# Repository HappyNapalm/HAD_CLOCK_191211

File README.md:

# HAD_CLOCK_191211 #
Clock for HAD Contest

## TODO ##
* Final verification of footprints. Last time!
* Sort out transformer
* Design an enclosure
* Add buttons to program the time (Research cap touch)
* Convert Mouser Project into csv

~~Microcontroller Corrections to PIC18F45K20~~

~~Consider making a version for the LPC804 as well as the PIC~~

~~Consider making multiple sheets for the schematic~~

~~Redo the outline in 4 x 15 pattern instead of a 3 x 20 pattern~~

## Parts to Select ##
* Transformer
* Diodes
* Resist0r 0603 100 ohm for 20 mAs at 3v3. 72 resistors

~~Shift Register (Affects resistor size)~~

~~Full rectifier~~

## Brief License ##
* Non-comericial
* Unlimited remakes for personal use
* Cite this project as source for any re-mixes

### Online Resources ###
https://www.pcbway.com/pcb_prototype/What_are_Plated_Half_Holes_Castellated_Holes_.html

### KiCAD Renders ###

Front | Back
:-------:|:------:
![Clock Front] (https://github.com/HappyNapalm/HAD_CLOCK_191211/blob/pic18/front.png)  |  ![Clock Rear] (https://github.com/HappyNapalm/HAD_CLOCK_191211/blob/pic18/rear.png)

![LED Test Front] (../renders/01_LED_test/front.png)

![LED Test Rear] (../renders/01_LED_test/rear.png)

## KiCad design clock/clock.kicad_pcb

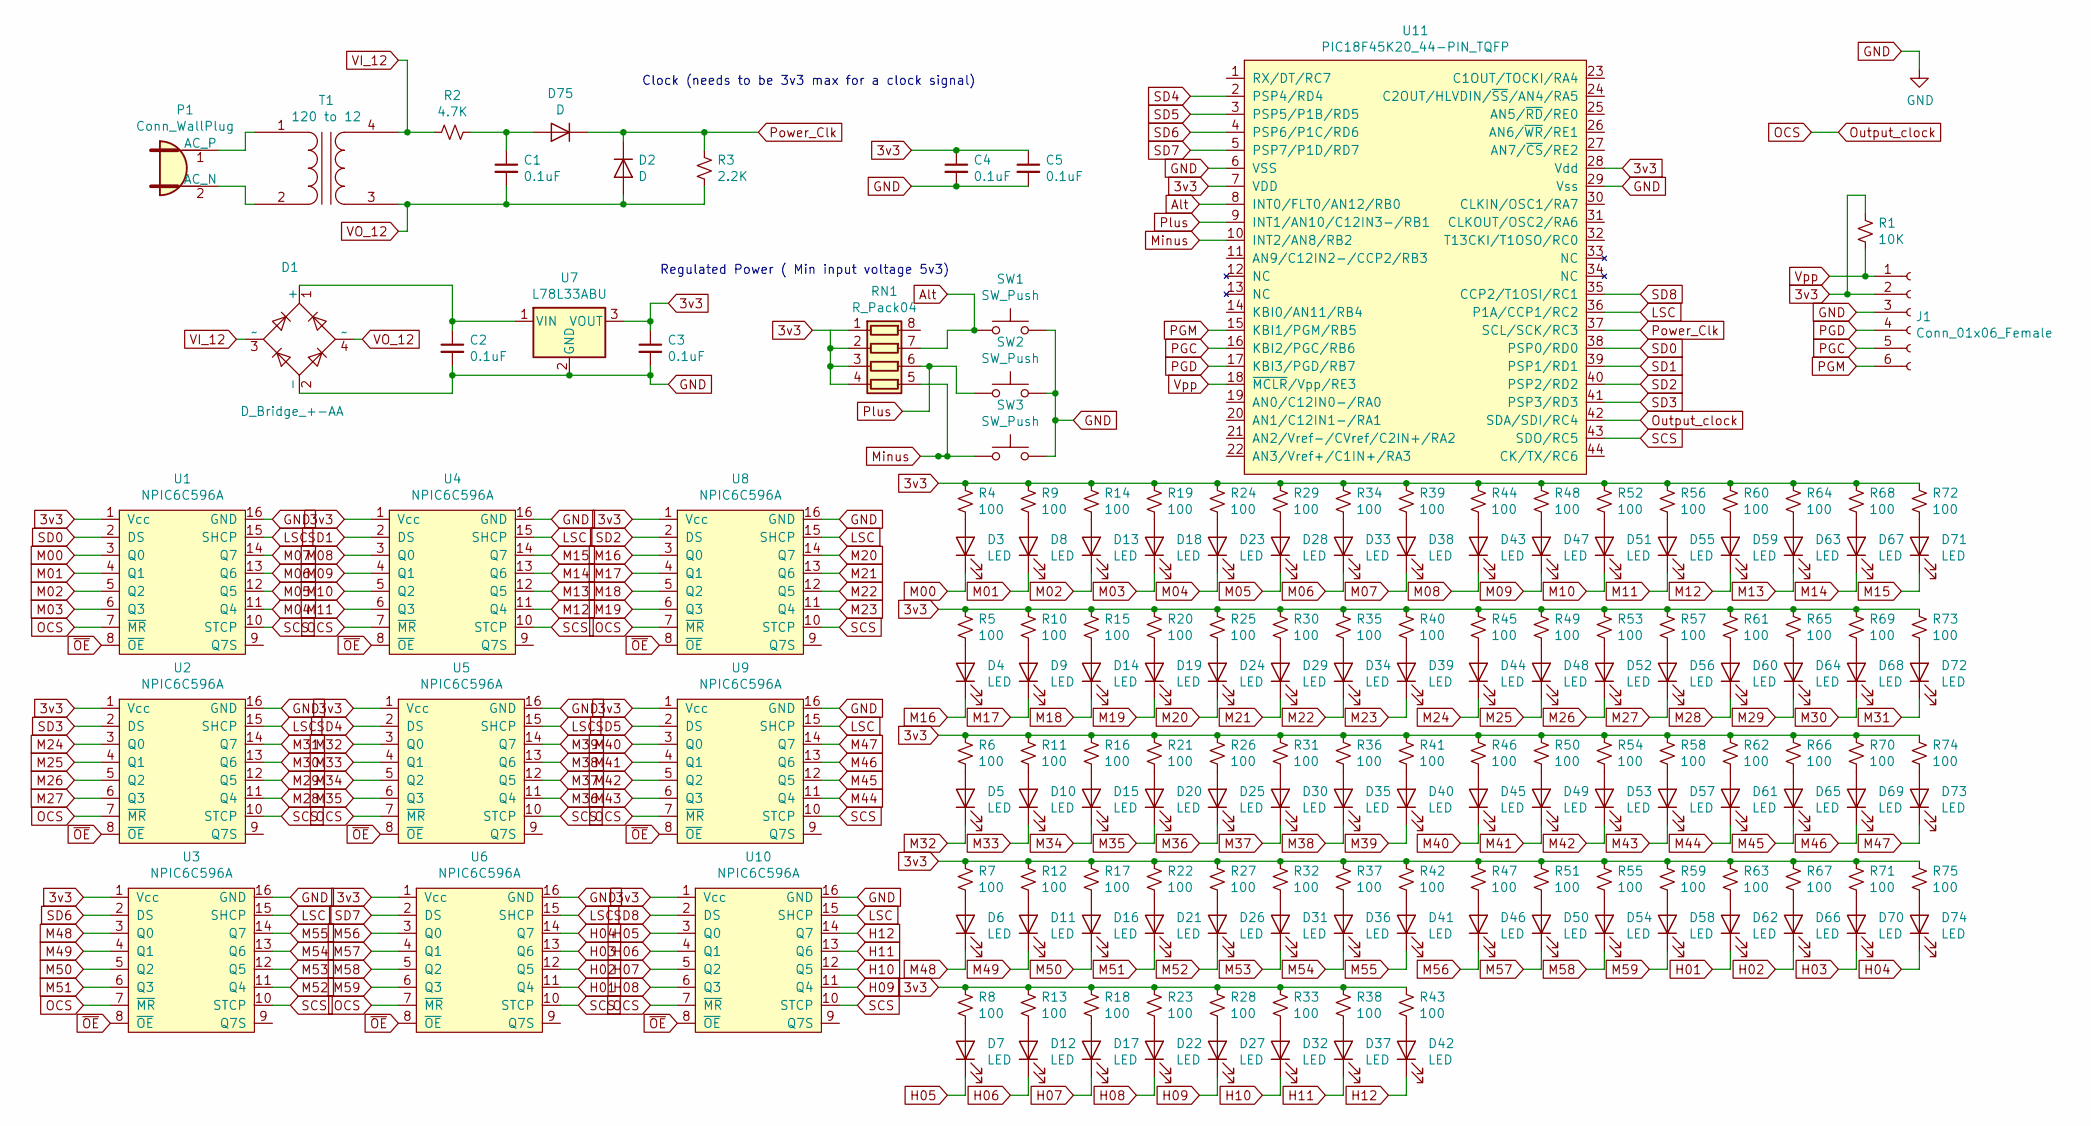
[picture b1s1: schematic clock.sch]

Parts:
C1, C2, C3, C4, C5: 0.1uF; C_0805_2012Metric
D1: D_Bridge_+-AA; Diode_Bridge_Diotec_ABS
D2, D75: D; D_0805_2012Metric
D3, D4, D5, D6, D7, D8, D9, D10, D11, D12, D13, D14, D15, D16, D17, D18, D19, D20, D21, D22, D23, D24, D25, D26, D27, D28, D29, D30, D31, D32, D33, D34, D35, D36, D37, D38, D39, D40, D41, D42, D43, D44, D45, D46, D47, D48, D49, D50, D51, D52, D53, D54, D55, D56, D57, D58, D59, D60, D61, D62, D63, D64, D65, D66, D67, D68, D69, D70, D71, D72, D73, D74: LED; LTST-S110KGKT_castellated_silkV1_rounded_rec
J1: Conn_01x06_Female; PinHeader_1x06_P2.54mm_Vertical
P1: Conn_WallPlug; PhoenixContact_GMSTBA_2,5_2-G-7,62_1x02_P7.62mm_Horizontal
R1: 10K; R_0805_2012Metric
R2: 4.7K; R_Axial_DIN0204_L3.6mm_D1.6mm_P7.62mm_Horizontal
R3: 2.2K; R_Axial_DIN0204_L3.6mm_D1.6mm_P7.62mm_Horizontal
R4, R5, R6, R7, R8, R9, R10, R11, R12, R13, R14, R15, R16, R17, R18, R19, R20, R21, R22, R23, R24, R25, R26, R27, R28, R29, R30, R31, R32, R33, R34, R35, R36, R37, R38, R39, R40, R41, R42, R43, R44, R45, R46, R47, R48, R49, R50, R51, R52, R53, R54, R55, R56, R57, R58, R59, R60, R61, R62, R63, R64, R65, R66, R67, R68, R69, R70, R71, R72, R73, R74, R75: 100; R_0603_1608Metric
RN1: R_Pack04; R_Array_Concave_4x0603
SW1, SW2, SW3: SW_Push; LL3301FF065QJ
T1: 120 to 12; TerminalBlock_bornier-2_P5.08mm
U1, U2, U3, U4, U5, U6, U8, U9, U10: NPIC6C596A; TSSOP-16_4.4x5mm_P0.65mm
U7: L78L33ABU; SOT-89-3
U11: PIC18F45K20_44-PIN_TQFP; TQFP-44_10x10mm_P0.8mm

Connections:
3v3: C3.1, C4.1, C5.1, J1.2, R1.1, R4.1, R5.1, R6.1, R7.1, R8.1, R9.1, R10.1, R11.1, R12.1, R13.1, R14.1, R15.1, R16.1, R17.1, R18.1, R19.1, R20.1, R21.1, R22.1, R23.1, R24.1, R25.1, R26.1, R27.1, R28.1, R29.1, R30.1, R31.1, R32.1, R33.1, R34.1, R35.1, R36.1, R37.1, R38.1, R39.1, R40.1, R41.1, R42.1, R43.1, R44.1, R45.1, R46.1, R47.1, R48.1, R49.1, R50.1, R51.1, R52.1, R53.1, R54.1, R55.1, R56.1, R57.1, R58.1, R59.1, R60.1, R61.1, R62.1, R63.1, R64.1, R65.1, R66.1, R67.1, R68.1, R69.1, R70.1, R71.1, R72.1, R73.1, R74.1, R75.1, RN1.1 (R1.1), RN1.2 (R2.1), RN1.3 (R3.1), RN1.4 (R4.1), U1.1 (Vcc), U2.1 (Vcc), U3.1 (Vcc), U4.1 (Vcc), U5.1 (Vcc), U6.1 (Vcc), U7.3 (VOUT), U8.1 (Vcc), U9.1 (Vcc), U10.1 (Vcc), U11.7 (VDD), U11.28 (Vdd)
Alt: RN1.7 (R2.2), SW1.1, U11.8 (INT0/FLT0/AN12/RB0)
GND: C2.2, C3.2, C4.2, C5.2, D1.2 (-), J1.3, SW1.2, SW2.2, SW3.2, U1.16 (GND), U2.16 (GND), U3.16 (GND), U4.16 (GND), U5.16 (GND), U6.16 (GND), U7.2 (GND), U8.16 (GND), U9.16 (GND), U10.16 (GND), U11.6 (VSS), U11.29 (Vss)
H01: D62.1 (K), U6.11 (Q4)
H02: D66.1 (K), U6.12 (Q5)
H03: D70.1 (K), U6.13 (Q6)
H04: D74.1 (K), U6.14 (Q7)
H05: D7.1 (K), U10.3 (Q0)
H06: D12.1 (K), U10.4 (Q1)
H07: D17.1 (K), U10.5 (Q2)
H08: D22.1 (K), U10.6 (Q3)
H09: D27.1 (K), U10.11 (Q4)
H10: D32.1 (K), U10.12 (Q5)
H11: D37.1 (K), U10.13 (Q6)
H12: D42.1 (K), U10.14 (Q7)
LSC: U1.15 (SHCP), U2.15 (SHCP), U3.15 (SHCP), U4.15 (SHCP), U5.15 (SHCP), U6.15 (SHCP), U8.15 (SHCP), U9.15 (SHCP), U10.15 (SHCP), U11.36 (P1A/CCP1/RC2)
M00: D3.1 (K), U1.3 (Q0)
M01: D8.1 (K), U1.4 (Q1)
M02: D13.1 (K), U1.5 (Q2)
M03: D18.1 (K), U1.6 (Q3)
M04: D23.1 (K), U1.11 (Q4)
M05: D28.1 (K), U1.12 (Q5)
M06: D33.1 (K), U1.13 (Q6)
M07: D38.1 (K), U1.14 (Q7)
M08: D43.1 (K), U4.3 (Q0)
M09: D47.1 (K), U4.4 (Q1)
M10: D51.1 (K), U4.5 (Q2)
M11: D55.1 (K), U4.6 (Q3)
M12: D59.1 (K), U4.11 (Q4)
M13: D63.1 (K), U4.12 (Q5)
M14: D67.1 (K), U4.13 (Q6)
M15: D71.1 (K), U4.14 (Q7)
M16: D4.1 (K), U8.3 (Q0)
M17: D9.1 (K), U8.4 (Q1)
M18: D14.1 (K), U8.5 (Q2)
M19: D19.1 (K), U8.6 (Q3)
M20: D24.1 (K), U8.14 (Q7)
M21: D29.1 (K), U8.13 (Q6)
M22: D34.1 (K), U8.12 (Q5)
M23: D39.1 (K), U8.11 (Q4)
M24: D44.1 (K), U2.3 (Q0)
M25: D48.1 (K), U2.4 (Q1)
M26: D52.1 (K), U2.5 (Q2)
M27: D56.1 (K), U2.6 (Q3)
M28: D60.1 (K), U2.11 (Q4)
M29: D64.1 (K), U2.12 (Q5)
M30: D68.1 (K), U2.13 (Q6)
M31: D72.1 (K), U2.14 (Q7)
M32: D5.1 (K), U5.3 (Q0)
M33: D10.1 (K), U5.4 (Q1)
M34: D15.1 (K), U5.5 (Q2)
M35: D20.1 (K), U5.6 (Q3)
M36: D25.1 (K), U5.11 (Q4)
M37: D30.1 (K), U5.12 (Q5)
M38: D35.1 (K), U5.13 (Q6)
M39: D40.1 (K), U5.14 (Q7)
M40: D45.1 (K), U9.3 (Q0)
M41: D49.1 (K), U9.4 (Q1)
M42: D53.1 (K), U9.5 (Q2)
M43: D57.1 (K), U9.6 (Q3)
M44: D61.1 (K), U9.11 (Q4)
M45: D65.1 (K), U9.12 (Q5)
M46: D69.1 (K), U9.13 (Q6)
M47: D73.1 (K), U9.14 (Q7)
M48: D6.1 (K), U3.3 (Q0)
M49: D11.1 (K), U3.4 (Q1)
M50: D16.1 (K), U3.5 (Q2)
M51: D21.1 (K), U3.6 (Q3)
M52: D26.1 (K), U3.11 (Q4)
M53: D31.1 (K), U3.12 (Q5)
M54: D36.1 (K), U3.13 (Q6)
M55: D41.1 (K), U3.14 (Q7)
M56: D46.1 (K), U6.3 (Q0)
M57: D50.1 (K), U6.4 (Q1)
M58: D54.1 (K), U6.5 (Q2)
M59: D58.1 (K), U6.6 (Q3)
Minus: RN1.5 (R4.2), SW3.1, U11.10 (INT2/AN8/RB2)
unnamed: C1.1, D75.2 (A), R2.1
unnamed: C2.1, D1.1 (+), U7.1 (VIN)
unnamed: D3.2 (A), R4.2
unnamed: D4.2 (A), R5.2
unnamed: D5.2 (A), R6.2
unnamed: D6.2 (A), R7.2
unnamed: D7.2 (A), R8.2
unnamed: D8.2 (A), R9.2
unnamed: D9.2 (A), R10.2
unnamed: D10.2 (A), R11.2
unnamed: D11.2 (A), R12.2
unnamed: D12.2 (A), R13.2
unnamed: D13.2 (A), R14.2
unnamed: D14.2 (A), R15.2
unnamed: D15.2 (A), R16.2
unnamed: D16.2 (A), R17.2
unnamed: D17.2 (A), R18.2
unnamed: D18.2 (A), R19.2
unnamed: D19.2 (A), R20.2
unnamed: D20.2 (A), R21.2
unnamed: D21.2 (A), R22.2
unnamed: D22.2 (A), R23.2
unnamed: D23.2 (A), R24.2
unnamed: D24.2 (A), R25.2
unnamed: D25.2 (A), R26.2
unnamed: D26.2 (A), R27.2
unnamed: D27.2 (A), R28.2
unnamed: D28.2 (A), R29.2
unnamed: D29.2 (A), R30.2
unnamed: D30.2 (A), R31.2
unnamed: D31.2 (A), R32.2
unnamed: D32.2 (A), R33.2
unnamed: D33.2 (A), R34.2
unnamed: D34.2 (A), R35.2
unnamed: D35.2 (A), R36.2
unnamed: D36.2 (A), R37.2
unnamed: D37.2 (A), R38.2
unnamed: D38.2 (A), R39.2
unnamed: D39.2 (A), R40.2
unnamed: D40.2 (A), R41.2
unnamed: D41.2 (A), R42.2
unnamed: D42.2 (A), R43.2
unnamed: D43.2 (A), R44.2
unnamed: D44.2 (A), R45.2
unnamed: D45.2 (A), R46.2
unnamed: D46.2 (A), R47.2
unnamed: D47.2 (A), R48.2
unnamed: D48.2 (A), R49.2
unnamed: D49.2 (A), R50.2
unnamed: D50.2 (A), R51.2
unnamed: D51.2 (A), R52.2
unnamed: D52.2 (A), R53.2
unnamed: D53.2 (A), R54.2
unnamed: D54.2 (A), R55.2
unnamed: D55.2 (A), R56.2
unnamed: D56.2 (A), R57.2
unnamed: D57.2 (A), R58.2
unnamed: D58.2 (A), R59.2
unnamed: D59.2 (A), R60.2
unnamed: D60.2 (A), R61.2
unnamed: D61.2 (A), R62.2
unnamed: D62.2 (A), R63.2
unnamed: D63.2 (A), R64.2
unnamed: D64.2 (A), R65.2
unnamed: D65.2 (A), R66.2
unnamed: D66.2 (A), R67.2
unnamed: D67.2 (A), R68.2
unnamed: D68.2 (A), R69.2
unnamed: D69.2 (A), R70.2
unnamed: D70.2 (A), R71.2
unnamed: D71.2 (A), R72.2
unnamed: D72.2 (A), R73.2
unnamed: D73.2 (A), R74.2
unnamed: D74.2 (A), R75.2
unnamed: P1.1 (AC_P), T1.1 (AA)
unnamed: P1.2 (AC_N), T1.2 (AB)
OCS: U1.7 (~MR), U2.7 (~MR), U3.7 (~MR), U4.7 (~MR), U5.7 (~MR), U6.7 (~MR), U8.7 (~MR), U9.7 (~MR), U10.7 (~MR), U11.42 (SDA/SDI/RC4)
PGC: J1.5, U11.16 (KBI2/PGC/RB6)
PGD: J1.4, U11.17 (KBI3/PGD/RB7)
PGM: J1.6, U11.15 (KBI1/PGM/RB5)
Plus: RN1.6 (R3.2), SW2.1, U11.9 (INT1/AN10/C12IN3-/RB1)
Power_Clk: D2.1 (K), D75.1 (K), R3.2, U11.37 (SCL/SCK/RC3)
SCS: U1.10 (STCP), U2.10 (STCP), U3.10 (STCP), U4.10 (STCP), U5.10 (STCP), U6.10 (STCP), U8.10 (STCP), U9.10 (STCP), U10.10 (STCP), U11.43 (SDO/RC5)
SD0: U1.2 (DS), U11.38 (PSP0/RD0)
SD1: U4.2 (DS), U11.39 (PSP1/RD1)
SD2: U8.2 (DS), U11.40 (PSP2/RD2)
SD3: U2.2 (DS), U11.41 (PSP3/RD3)
SD4: U5.2 (DS), U11.2 (PSP4/RD4)
SD5: U9.2 (DS), U11.3 (PSP5/P1B/RD5)
SD6: U3.2 (DS), U11.4 (PSP6/P1C/RD6)
SD7: U6.2 (DS), U11.5 (PSP7/P1D/RD7)
SD8: U10.2 (DS), U11.35 (CCP2/T1OSI/RC1)
VI_12: D1.3 (~~), R2.2, T1.4 (SB)
VO_12: C1.2, D1.4 (~~), D2.2 (A), R3.1, T1.3 (SA)
Vpp: J1.1, R1.2, U11.18 (~MCLR~/Vpp/RE3)
~OE: U1.8 (~OE), U2.8 (~OE), U3.8 (~OE), U4.8 (~OE), U5.8 (~OE), U6.8 (~OE), U8.8 (~OE), U9.8 (~OE), U10.8 (~OE)

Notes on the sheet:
Clock (needs to be 3v3 max for a clock signal)
Regulated Power ( Min input voltage 5v3)

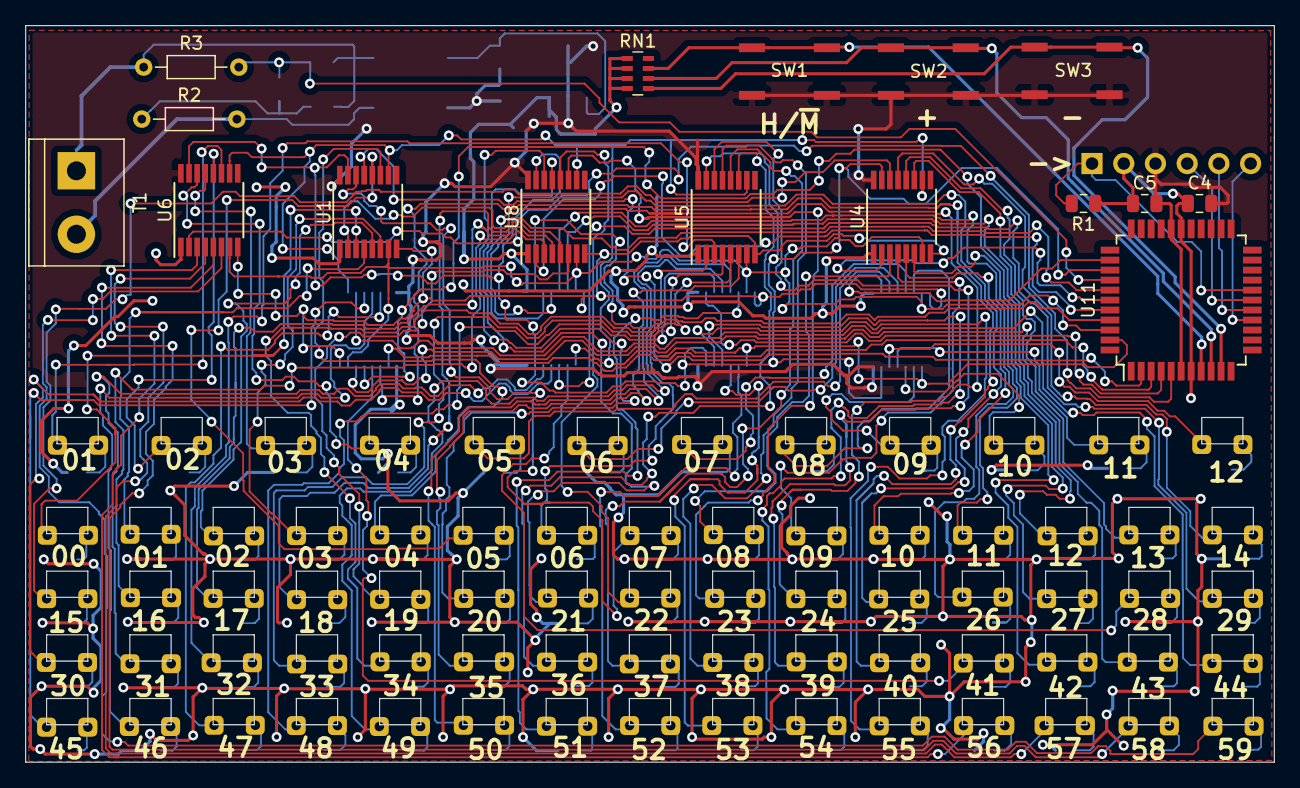
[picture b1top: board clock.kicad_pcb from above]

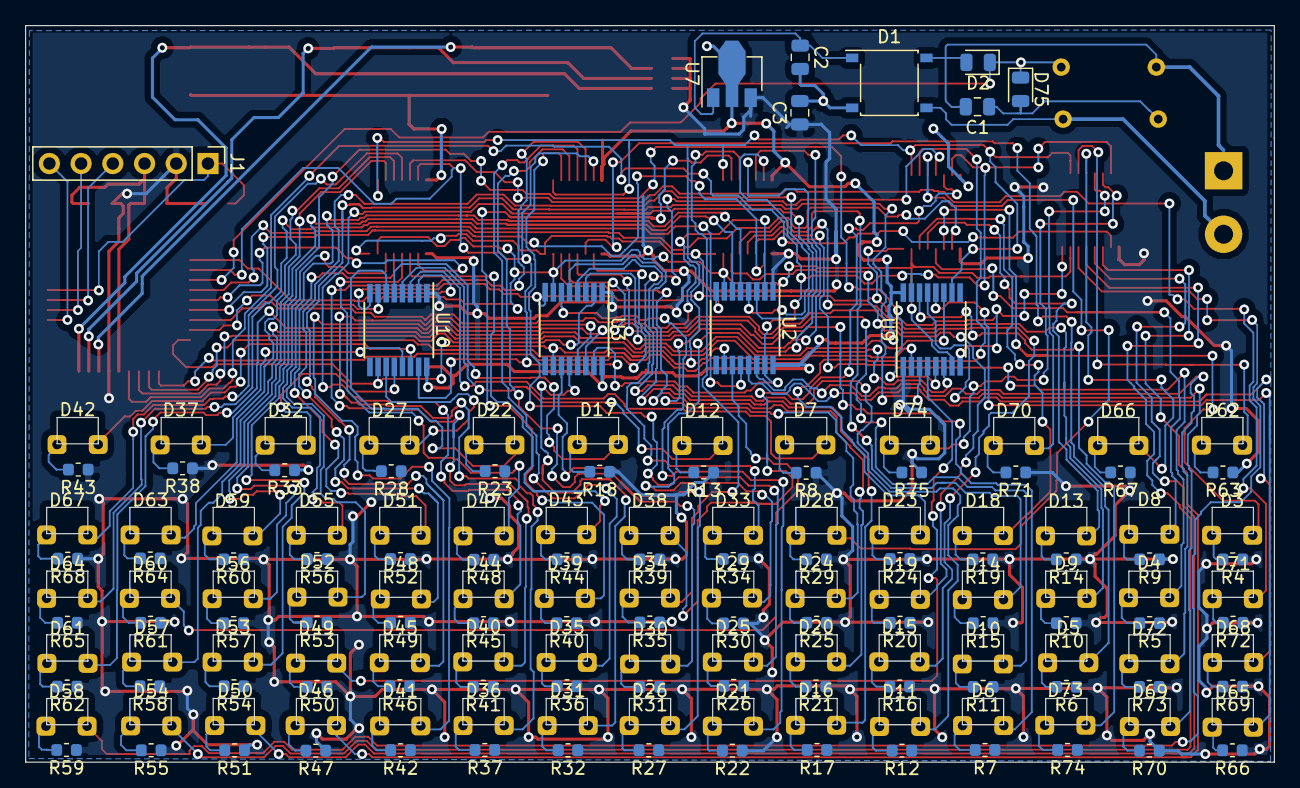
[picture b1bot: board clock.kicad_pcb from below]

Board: 2 copper layers, 100.0 x 59.0 mm, 172 parts (156 on the bottom side), 171 nets.

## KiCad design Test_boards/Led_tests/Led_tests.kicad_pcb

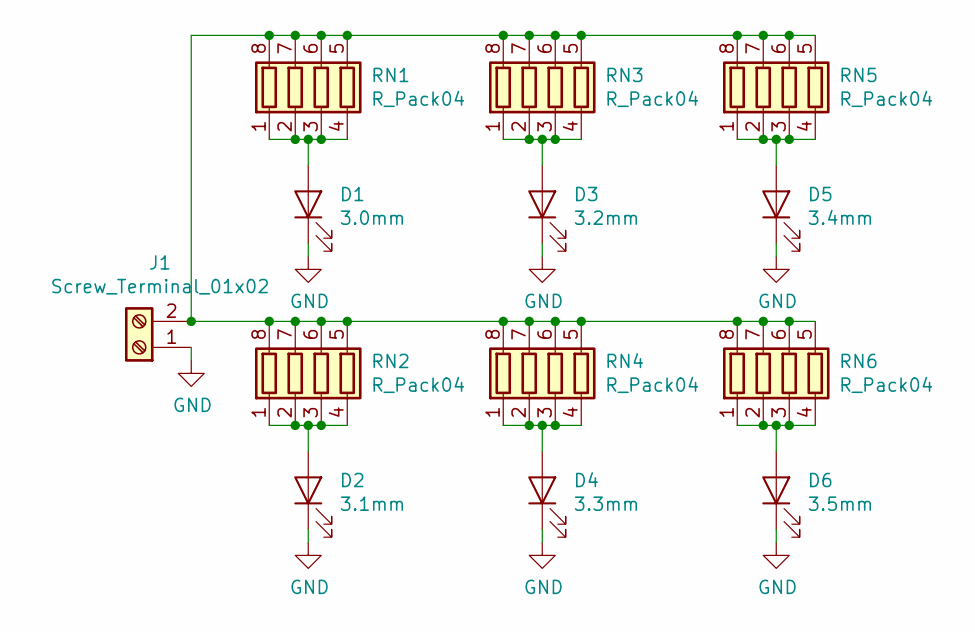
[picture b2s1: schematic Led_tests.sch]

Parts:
D1: 3.0mm; LTST-S110KGKT_castellated_3.0mm
D2: 3.1mm; LTST-S110KGKT_castellated_3.1mm
D3: 3.2mm; LTST-S110KGKT_castellated_3.2mm
D4: 3.3mm; LTST-S110KGKT_castellated_3.3mm
D5: 3.4mm; LTST-S110KGKT_castellated_3.4mm
D6: 3.5mm; LTST-S110KGKT_castellated_3.5mm
J1: Screw_Terminal_01x02; TerminalBlock_bornier-2_P5.08mm
RN1, RN2, RN3, RN4, RN5, RN6: R_Pack04; R_Array_Concave_4x0603

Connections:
GND: D1.1 (K), D2.1 (K), D3.1 (K), D4.1 (K), D5.1 (K), D6.1 (K), J1.1
unnamed: D1.2 (A), RN1.1 (R1.1), RN1.2 (R2.1), RN1.3 (R3.1), RN1.4 (R4.1)
unnamed: D2.2 (A), RN2.1 (R1.1), RN2.2 (R2.1), RN2.3 (R3.1), RN2.4 (R4.1)
unnamed: D3.2 (A), RN3.1 (R1.1), RN3.2 (R2.1), RN3.3 (R3.1), RN3.4 (R4.1)
unnamed: D4.2 (A), RN4.1 (R1.1), RN4.2 (R2.1), RN4.3 (R3.1), RN4.4 (R4.1)
unnamed: D5.2 (A), RN5.1 (R1.1), RN5.2 (R2.1), RN5.3 (R3.1), RN5.4 (R4.1)
unnamed: D6.2 (A), RN6.1 (R1.1), RN6.2 (R2.1), RN6.3 (R3.1), RN6.4 (R4.1)
unnamed: J1.2, RN1.5 (R4.2), RN1.6 (R3.2), RN1.7 (R2.2), RN1.8 (R1.2), RN2.5 (R4.2), RN2.6 (R3.2), RN2.7 (R2.2), RN2.8 (R1.2), RN3.5 (R4.2), RN3.6 (R3.2), RN3.7 (R2.2), RN3.8 (R1.2), RN4.5 (R4.2), RN4.6 (R3.2), RN4.7 (R2.2), RN4.8 (R1.2), RN5.5 (R4.2), RN5.6 (R3.2), RN5.7 (R2.2), RN5.8 (R1.2), RN6.5 (R4.2), RN6.6 (R3.2), RN6.7 (R2.2), RN6.8 (R1.2)

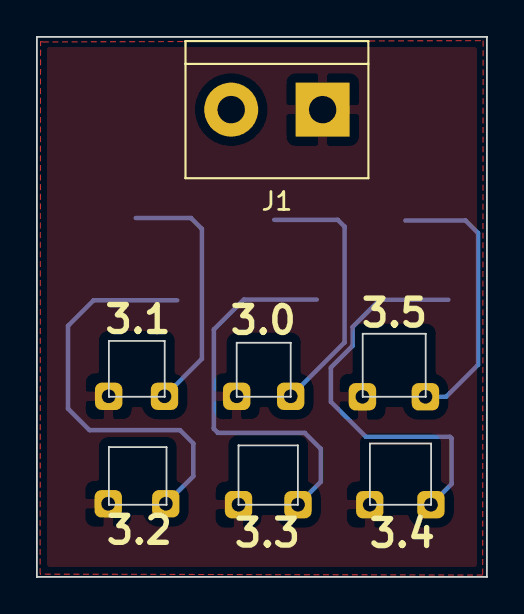
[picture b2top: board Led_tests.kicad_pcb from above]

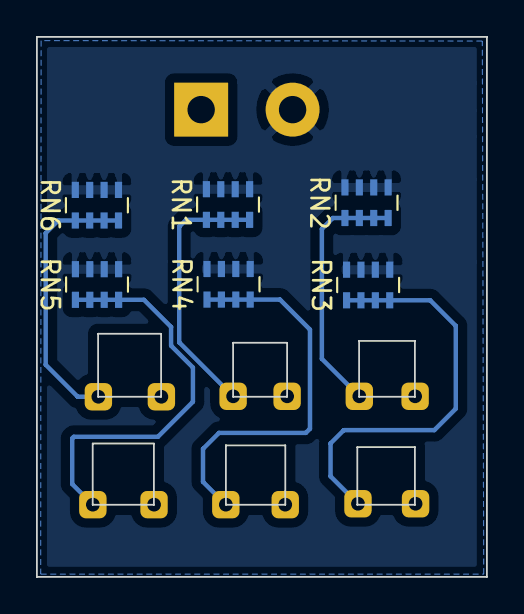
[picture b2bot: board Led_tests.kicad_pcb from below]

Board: 2 copper layers, 25.0 x 30.0 mm, 13 parts (6 on the bottom side), 8 nets.

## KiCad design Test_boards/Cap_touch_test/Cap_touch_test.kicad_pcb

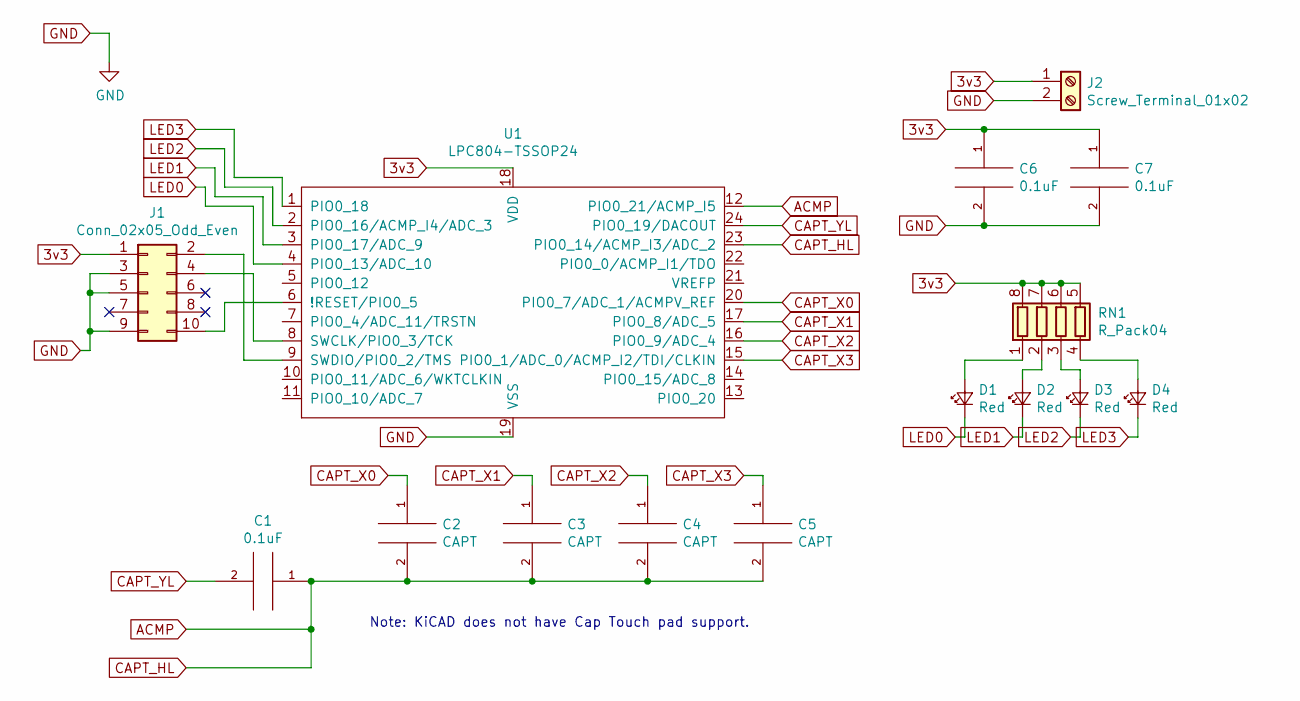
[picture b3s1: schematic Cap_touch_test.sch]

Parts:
C1, C6, C7: 0.1uF; C_0805_2012Metric
C2, C3, C4, C5: CAPT; Cap_T_pad_v1.1
D1, D2, D3, D4: Red; D_0805_2012Metric
J1: Conn_02x05_Odd_Even; PinHeader_2x05_P1.27mm_Vertical
J2: Screw_Terminal_01x02; TerminalBlock_bornier-2_P5.08mm
RN1: R_Pack04; R_Array_Concave_4x0603
U1: LPC804-TSSOP24; TSSOP-24_4.4x7.8mm_P0.65mm

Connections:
3v3: C6.1, C7.1, J1.1, J2.1, RN1.5 (R4.2), RN1.6 (R3.2), RN1.7 (R2.2), RN1.8 (R1.2), U1.18 (VDD)
ACMP: C1.1, C2.2, C3.2, C4.2, C5.2, U1.12 (PIO0_21/ACMP_I5), U1.23 (PIO0_14/ACMP_I3/ADC_2)
CAPT_X0: C2.1, U1.20 (PIO0_7/ADC_1/ACMPV_REF)
CAPT_X1: C3.1, U1.17 (PIO0_8/ADC_5)
CAPT_X2: C4.1, U1.16 (PIO0_9/ADC_4)
CAPT_X3: C5.1, U1.15 (PIO0_1/ADC_0/ACMP_I2/TDI/CLKIN)
CAPT_YL: C1.2, U1.24 (PIO0_19/DACOUT)
GND: C6.2, C7.2, J1.3, J1.5, J1.9, J2.2, U1.19 (VSS)
LED0: D1.1 (K), U1.4 (PIO0_13/ADC_10)
LED1: D2.1 (K), U1.3 (PIO0_17/ADC_9)
LED2: D3.1 (K), U1.2 (PIO0_16/ACMP_I4/ADC_3)
LED3: D4.1 (K), U1.1 (PIO0_18)
unnamed: D1.2 (A), RN1.1 (R1.1)
unnamed: D2.2 (A), RN1.2 (R2.1)
unnamed: D3.2 (A), RN1.3 (R3.1)
unnamed: D4.2 (A), RN1.4 (R4.1)
unnamed: J1.2, U1.9 (SWDIO/PIO0_2/TMS)
unnamed: J1.4, U1.8 (SWCLK/PIO0_3/TCK)
unnamed: J1.10, U1.6 (!RESET/PIO0_5)

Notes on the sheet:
Note: KiCAD does not have Cap Touch pad support.

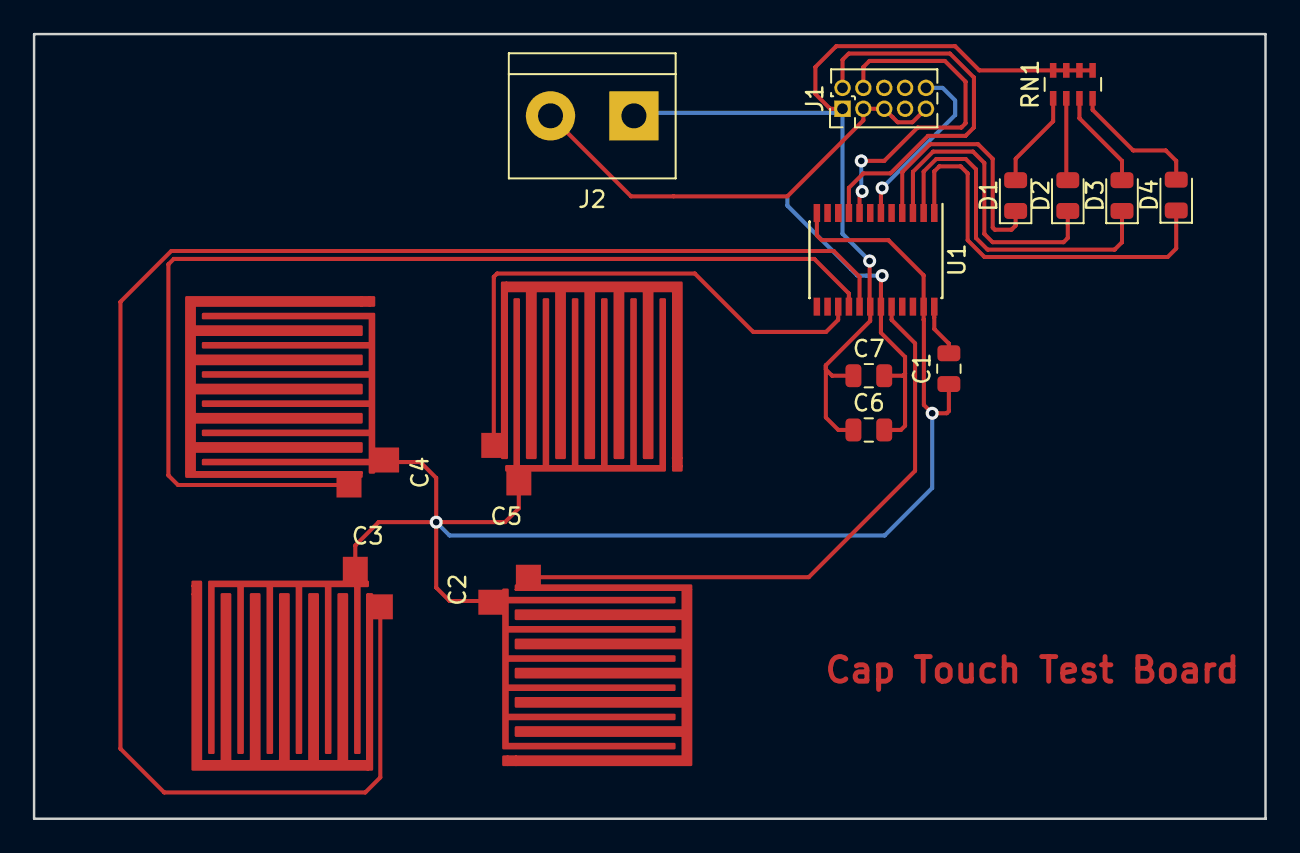
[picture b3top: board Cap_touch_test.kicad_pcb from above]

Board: 2 copper layers, 75.0 x 47.8 mm, 15 parts (0 on the bottom side), 19 nets.

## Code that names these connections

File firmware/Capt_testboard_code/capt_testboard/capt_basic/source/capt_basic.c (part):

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    // GPIO_PortSet(GPIO, 0U, 1U << 15U);
    // GPIO_PortSet(GPIO, 0U, 1U << 8U);
    // GPIO_PortSet(GPIO, 0U, 1U << 9U);
    GPIO_PortSet(GPIO, 0U, 1U << 18);   //LED3
    GPIO_PortSet(GPIO, 0U, 1U << 16);   //LED2
    GPIO_PortSet(GPIO, 0U, 1U << 17);   //LED1
    GPIO_PortSet(GPIO, 0U, 1U << 13);   //LED0
}

/*!
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
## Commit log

2019-12-12 Add files via upload
    Local files
2019-12-12 Bare bones of clock schematic made
2019-12-12 Added rough todo list to the readme
2019-12-12 Selected to use the LPC804 over the PIC18F45k20
2019-12-13 Selecting serial data lines impressed the importance of selecting appropriate pins for my cap touch
2019-12-13 Update README.md
    Updated Readme with mark up. Different from bitbucket...
2019-12-14 Selected 596 shift register. Redid LED schematics. Started bom. Updated readme todo list
2019-12-14 Worked on all LED and 596 nets before realizing that I was on the wrong branch. Going to push on branch 191311 and then switch my local back to the master branch
2019-12-17 Decided on a full wave rectifier. Reevaluated the desired transformer and chose a 120 to 12. Reevaluation due to minimum vin on 3v3 rec is 5v3. Added simulations images from QUCS to the build. QUCS u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
2019-12-17 Removed LibreOffice temp file
2019-12-17 Added QUCS sim files to the project repo
2019-12-17 Updated TODO to match the work that has been done
2019-12-17 Correct QUCS sim to adhere more to reality. Noticed incongruity between 596 foot print and default KiCAD schematic symbol.
2019-12-18 Working on placing all 72 castellated holes for the LEDs.
2019-12-18 After placing the castellated holes, a problem was discovered with routing. This will require a redesign of the edge layer.
2019-12-18 Saving progress on converting outline from 3 x 20 to 4 x 15
2019-12-18 Finished conversion of FreeCAD layout from 3x20 to 4x15
2019-12-18 Updated TODO
2019-12-18 Working on moving the castellated holes to the new outline. Saving progress.
2019-12-18 Saving progress made on placing parts. Note: concern to routing space. Consider 6/6 rules and think of going up to 5/5 rules
2019-12-18 Finished rough part placement. Need to review Transformer. Need to address potential routing issue.
2019-12-19 Routing discipline broke down very early. I am going to ride this wave until it is too maddening
2019-12-19 Confirmed that current routing plan will not work. TODO re-place the shift registers. Attempt to limit 'roll over'
2019-12-19 Converted the 0805 to 0603. Ripped up previous routing
2019-12-19 Working on fixing the routing on 6/6 rules. I am worried about power
2019-12-20 Finished some layout. 'Rollover' is kicking my butt. May consider using jumpers as a 3rd layer
2019-12-21 Saving progress
2019-12-21 Saving routing progress
2019-12-21 Saving routing progress. 50% done
2019-12-22 29/72 LEDs remaining.
2019-12-22 Saving progress 191221
2019-12-23 ~21 left
2019-12-23 Now we are at the hardest LEDs
2019-12-23 progress saving
2019-12-24 10 LEDs left
2019-12-24 2 more collums of LEDs
2019-12-27 Ran into a trace width issue. Default kicad trace width is 0.25mm or about 9mils. PCBWay can handle 6 mil space or 0.15mm. So I am reducing the traces down to 6 mils. All of them. I am commiting the 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
2019-12-27 Found the automatic setting to update all trace widths.
2019-12-27 All LEDs routed. Will consider some optimization e.g. via reduction or shorting traces.
2019-12-27 Moving to a new work.
2019-12-27 Added Renders
2019-12-27 Making proof of concept boards before going too much crazier
2019-12-27 Completed LED castellated hole test board
2019-12-27 Generated Gerbers for LED test board. Created proj dir for cap touch test board
2019-12-27 Made schematic for the cap touch test based on the LPC804 app notes
2019-12-27 saving progress.
2019-12-27 Adding Cap Touch design docs to the repo. May be removed at a later date.
2019-12-28 Complicated pads are beyond my skills at the moment. I will need to create something of 'fill zones'. I reached out some feelers on hackaday but I am proceeding with my current information.
2019-12-30 Added Renders
    Added Renders to the markdown file.
2019-12-30 Learning markdown
2020-01-02 Added test cap touch pads to test board. Added renders. Review before initial submission to PCBway for manufacturing.
2020-01-03 Test boards submitted to PCBway for review and approval.
2020-01-04 addressed error in outline of LED_test board
2020-01-16 Added demo firmware from the NXP demo libs
2020-01-16 Modified LED section of the code. Will need to read over demo board schema in order to verify pin_mux files
2020-01-16 I think I know what to do
2020-01-16 saving progress on my io define changes
2020-01-18 Converted the process from LPC804 to PIC18F45K20 due to time constraints.
2020-01-18 Updated todo list and some tracing
2020-01-18 Verified the part selected for shift registers. The part is way off. Updated Schematic. Updating PCB lay out.
2020-01-18 removing csv temp file
2020-01-20 Reroute the shift registers
2020-01-20 Routing update incomplete.
2020-01-20 Need to route power. Considering expanding the board.
2020-01-20 TODO: Trace power domains.
2020-01-20 2 more traces. Need to add the transformer tabs.
2020-01-21 Setup gerbers
2020-01-21 Gerbers sent to JLCPCB.

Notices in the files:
firmware/Capt_testboard_code/capt_testboard/capt_basic/source/capt_basic.c:
Copyright 2017 NXP
All rights reserved.
SPDX-License-Identifier: BSD-3-Clause
